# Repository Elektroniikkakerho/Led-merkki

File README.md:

# LED-MERKKI

## Mistä koostuu ja miten se toimii
Salaman mikrokontrolleri (mcu) ohjaa ledejä sytyttäen niitä yksi kerrallaan hyvin lyhyeksi aikaa.
Ledit ovat multiplexattu (4x8 LED), ja kytketty yhdellä vastuksella per rivi.

Levyyn on myös suunniteltu kytkin, jolla voisi vaikka sammuttaa laitteen tai toimittaa muuta toiminnallisuutta, mutta näitä ei ole koodissa toteutettu vieläkään.

Kuusipinninen liitin on ohjelmointia varten ja sitä kautta ohjelma siirretääm mikrokontrollerille.
Ohjelmointi hoituu Arduinon ISP:n kautta.

## Skeema

## Osaluettelo
<!--
  * 1 kpl  ATtiny861a SOIC
  * 32 kpl 3 mm diffusoitu LED
  * 1 kpl  10 µF SMD tantaalikondensaattori
  * Kuusi pinnisen piikkiriman ohjelmointia varten.

  **Riippuen LEDien väristä:**
  * Siniset/valkoiset/vihreät:   4 kpl 110 Ohm 1206/1210 SMD-vastus
  * Punaiset/keltaiset:          4 kpl 150 Ohm...
  
  **lisäksi tarvitset:**
  * kuumaliimaa
  * USB kaapelin
  * Extra vastuksen? Selivä myöhemmin...
  * haalarimerkin :-)
-->

| **Komponetti** | **KPL** | **Huomautukset** |
| :--- | :--- | :--- |
| ATtiny861a SOIC | 1 |  |
| 3 mm diffusoitu LED | 32 | |
| 110 Ohm 1206/1210 SMD vastus | 4 | Sinisille, valkoisille, vihreille ledeille |
| 169 Ohm 1206/1210 SMD vastus | 4 | Keltaisille, punaisille ledeille |
| 10 µF SMD tantaalikondensaattori | 1 | |
| 6 pinnisen piikkirima | - | Ohjelmointia varten |
| Kuumaliimaa | - | Ledien suojaamiseen |
| USB kaapeli | - | Sopivan pituinen, vaikka 1 m |
| Haalarimerkki | 1 | :-) |

<!---
| **Komponetti** | **KPL** | **Huomautukset** |
| :--- | :--- | :--- |
| ATtiny861a SOIC | 1 | S/SU |
| 3 mm diffusoitu LED | 32 | |
| 10 µF SMD tantaalikondensaattori | 1 | |

| **Vastuksets** | **KPL** | **Huomautukset** |
 :--- | :--- | :--- |
| 110 Ohm 1206/1210 SMD vastus | 4 | Sinisille, valkoisille, vihreille ledeille |
| 150 Ohm 1206/1210 SMD vastus | 4 | Keltaisille, punaisille ledeille |
| | | | 

| **Lisäksi tarvitset** | |
 :--- | :--- |
| 6 pinnisen piikkirima | ohjelmointia varten |
| Kuumaliimaa | Ledien suojaamiseen |
| USB kaapelin | Sopivan pituinen |
| Haalarimerkin  | :-) |
--->
  
## Pirilevyt 
| [SIK](kicad/possu) | OTiT | [YRK](kicad/ymp) | [PROSE](kicad/prose) | [KONE](kicad/kone) | [ARK](kicad/ark) | [OPTIEM](kicad/optiem) |
| :---: | :---: | :---: | :---: |  :---: |  :---: |  :---: |
|   |   |   |  |  |  |  <tr></tr>
|  |  |  |  |  |   | 
<!---|   |   |   |   | | | <tr></tr> --->

<!-- ## Ohjeet piirilevyn tekoon -->
<!-- <details> -->
<!-- <summary><b>Näytä </b></summary> -->
<!-- Tee vaikka syövyttämällä tai jyrsimällä :D -->
<!-- </details> -->

# Ohjeet kokoonpanoon

Nyt kun sinulla on piirilevy, laitetaampa siihen komponentit kiinni.

## 1. Pintaliitos komponentit

Piirilevyyn juotetaan 4 SMD vastusta, 1 SMD kondensaattori ja 6-pinninen piikkirimai.  
Helpointen ja nätein tapa juottaa ne on laittamalla yhteen pädiin vähän tinaa ja sitten     varovasti työntää komponetti sulaneseen tinaan, niin ettei se jää "ilmaan".  
Toinen puoli on helpompi juottaa kun se nyt pysyy siinä paikallaan.

Vastuksilla ei ole väliä kummin päin ne on laitettu, kuhan numero puoli on ylöspäin ja suhteellisen suoraan laitettu, se on hyvä.
Kondensaattorin suunta pitää kattoa leiskasta.

Piikkiriman juottaminen onnistuu samalla tavalla, paitsi nyt joudut pitämään sitä vähän ilmassa,  
jotta saat sen kunnolla juotettua kiinni.

## 2. Piiri 
Piirin juottaminen onnistuu helpointen siten, että juotat ensin yhden kulmajalan kiinni.  
Sulata juotos, jos piiri on vinossa.
Tarkista, että piirin kaikki jalat ovat pädien päällä. Ei ilmassa.  
Juota sitten toinen vastakkainen kulmajalma.

Loput jalat voi juottaa yksi kerrallaan.  
Tai jos haluaa kokeilla nopeammalla tavalla niin veto juottamalla saa yhden puolen yhdellä vedolla*. 
[Esimerkki video...](https://www.youtube.com/results?search_query=drag+soldering)

## 3. Virtajohto
USB kaapelista pitää leikata toinen pää pois.  
Kuori 5v and GND johdot joko saksilla tai kuorimilla.  
Juota sitten 5V ja GND piirilevyyn.

Tähän kannattaa käyttää USB-kaapelia, jossa on vain 5V ja GND.   
Tai sellaista kaapelia jossa on paksut sisäiset johtimet.

## 4. Ledit

Ledien juottaminen on suurin työmaa merkin valmistuksessa.  
Työtä aiheuttaa lähinnä ledin painaminen merkistä läpi. Ensin pitää huomioida polariteetti.  
Jos olet nähnyt paljon vaivaa että olet laittanut ledit miten sattuu niin voipi harmittaa..

**Pidä mielessä:**  
Pyöreä läpiveto ja pidempi jalka ledissä = POS  
Neliö läpiveto ja lyhyempi jalka ledissä = NEG

Ledien jalkojen päät kannattaa katkoa kulmassa, näin niistä tulee teräviä. Helpottaa ledien painamista merkistä läpi.
Toinen kikka on myös paksummalla neulalla tehä reikiä etukäteen.

Jos jostakin syystä, olet juottanut kaikki ledin väärin päin.  
Erinomaista, homma meni pieleen.  
Onneksi on olemassa toinen koodi tiedosto joka vaihtaa ledien logiikan.
   
## [5. Hyppää kohtaan "Ohjelmointi"](#ohjelmointi)
   
## 6. Piikkiriman poisto
Sitten kun ohjelmisto on flashatty ja tarkistettu, että kaikki ledit toimiii niinkuin pitäisi, piikkirima otetaan pois. Joko imusukkaa / tinapumppua käyttäen tai sitten lämmittämällä kaikki joloissa olevat tinat kolvilla, tekemällä vetoliikkeitä.
    
## 7. Kuormavastus 
Tässä kohtaan on hyvä kokeilla laittaa merkki powerbankkiin kiinni.

Jos merkki sammuu itsestään, se voi hyvinkin johtua siitä, että merkki on liian energiatehokas :D
Esim. SIK:in possu merkki syöpi n. 5-20 ma riippuen ledien tilasta.

Tämän ongelman saa korjattua juottamalla kuormavastuksen 5V ja GND väliin.  
Esim. Juottamalla 110 ohmin vastuksen, merkki syö ~60 ma.  
Tarvittava kuormavastus riippuu käyttämästäsi varavirtalähteestä.  
Niissä on vaihteleva minimivirranvaatimus, jonka alittaessa ne katkaisevat virransyötön.
    
## 8. Viimeistely
Lopuksi, laita kuumaliimaa ledien ympärille suojausta varten.  
Ei ole pakko jos et halua.

Mutta siinähän ois ***komia*** merkki valmiina.  
Ei muuta ku ompelemaan kiinni!!  
🥳 🧵 🪡

<!-- </details> -->

# Ohjelmointi

Tähän tarvitset Arduino nanon tai unon, jotta saat siirrettyä koodit levylle.

Koodin kääntämiseen tarvitset avr-gcc ja koodin siirtämiseen avrdude.  
Eli asenna omalle käyttöjärjestelmälle kyseiset työkalut, ennen seuraavia kohtia.

## 1. Ohjelmoinin setuppaus
Aletaanpa pukata sitä koodia, että merkkistä tulisi valoa.  
Mutta ensin pitää hyppyjohdoilla tehdä yhteys led-merkkiin.

Käytetään Arduino nanoa tässä esimerkissä:

| Merkin pinni | 1 | 2| 3 | 4 |5 |6 |
| :---: | :---: | :---: | :---: | :---: | :---: | :---: |
| *Selite* | *MOSI* | *MISO* | *SCK* | *VCC* | *GND* | *Reset* <tr></tr> |
| **Arduinon pinni** | **D11** | **D12**| **D13** | **VCC** | **GND** | **D10** | 

(Leiska kuvasta näkee liittimessä neliön --> 1. pinni)

Muista vetää arduinon Reset ylös. Ardu nollautuu kun sarjaliikenne alotetaan....

## 2. Ledien suunta logiikan flippaus
Mikäli olet juottanut ledit väärinpäin, eikä niiden irroittaminen ja uudelleen juottaminen huvita,  
voit muuttaa ledien ohjaavan logiikan ennen kääntämistä.
      
**Tiedosto: led-merkki/src/vilkutus.c**  
(rivit 6-7):

```c
#include "lediportit.h"             // Mikäli juotit ledit väärin päin,
// #include "lediportit_vaarin.h"   // Vaihda tästä otsikko tiedosto.
  ```
Ledit väärinpäin: 
```c
// #include "lediportit.h"             // Mikäli juotit ledit väärin päin,
#include "lediportit_vaarin.h"   // Vaihda tästä otsikko tiedosto.       
```

## 3. Koodin kääntäminen

```bash
# Kääntäminen käyttäen avr-gcc:tä
avr-gcc -mmcu=attiny861 salama.c -I./ -Os -DF_CPU=8000000UL
```

  Jos et saa koodeja käännettyä,  pre_compiled hakemistosta löytyy valmiiksi käännetyt koodit. 
    
## 4. Ohjelman siirto levylle 

#####  Unix-like

```bash
# Fläsäys käyttäen arduino-isp:tä
avrdude -c avrisp -p t861 -B3 -P /dev/ttyUSB0 -b 19200 -U flash:w:a.out

# Fuse asetukset käyttäen arduino-isp:tä
avrdude -c avrisp -p t861 -B3 -P /dev/ttyUSB0 -b 19200 -U lfuse:w:0xe2:m -U hfuse:w:0xdf:m
```
Jos valittaa oikeuksista, vedä sudo/doas tilassa.

Jos siirtämisen aikana tulee "programmer not responding",  
kokeile toista baudratea tai ottamalla "-B3" pois.

##### Windows

```bash
# Fläsäys käyttäen arduino-isp:tä
avrdude -c avrisp -p t861 -P COM3 -b 19200 -U flash:w:a.out

# Fuse asetukset käyttäen arduino-isp:tä
avrdude -c avrisp -p t861 -P COM3 -b 19200 -U lfuse:w:0xe2:m -U hfuse:w:0xdf:m

```
Windowsilla avrdude pitää olla ympäristömuuttujissa.  
Toinen vaihtoehto on ajaa komento "\Arduino\hardware\tools\avr\bin"-kansiossa.

Jos siirtämisen aikana tulee error,  
kokeile toista baudratea tai lisäämällä "-B3" kuten Unix-like komennoissa.

## [5. Hyppää kohtaan "Piikkiriman poisto"](#6-piikkiriman-poisto)

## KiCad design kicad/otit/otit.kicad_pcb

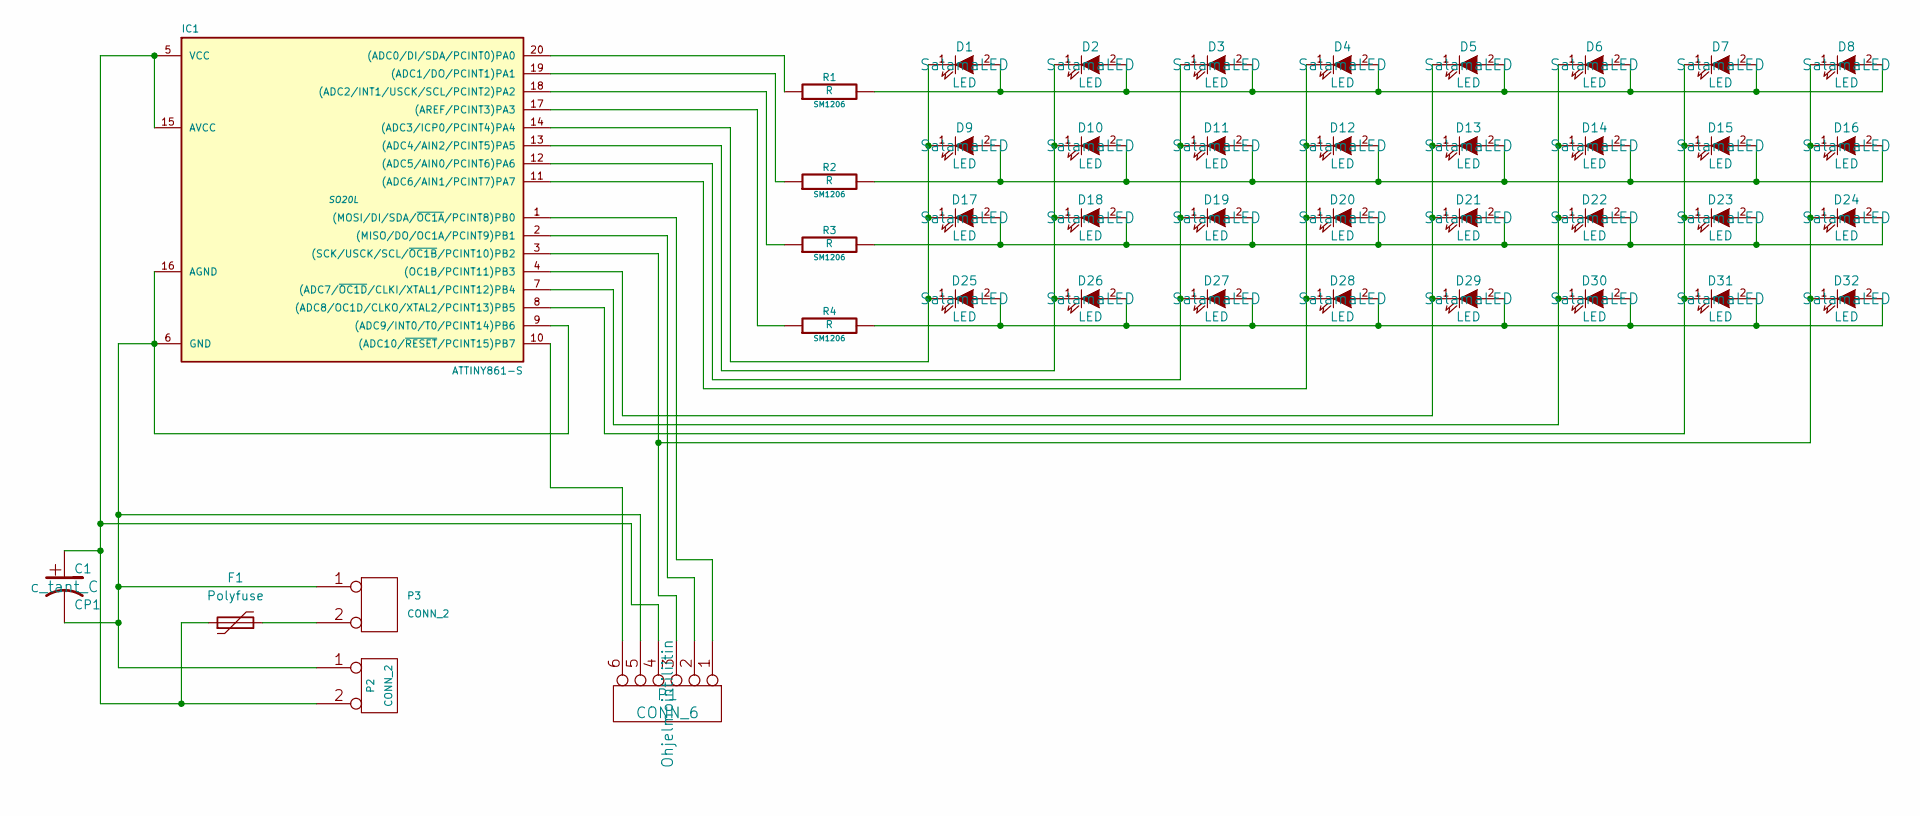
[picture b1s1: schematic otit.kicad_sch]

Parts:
C1: CP1; c_tant_C
D1, D2, D3, D4, D5, D6, D7, D8, D9, D10, D11, D12, D13, D14, D15, D16, D17, D18, D19, D20, D21, D22, D23, D24, D25, D26, D27, D28, D29, D30, D31, D32: LED; SalamaLED
F1: Polyfuse
IC1: ATTINY861-S; SO20L
P1: CONN_6; Ohjelmointiliitin
P2: CONN_2; Salama_virta
P3: CONN_2
R1, R2, R3, R4: R; SM1206

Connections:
unnamed: D1.2 (A), D2.2 (A), D3.2 (A), D4.2 (A), D5.2 (A), D6.2 (A), D7.2 (A), D8.2 (A), R1.2
unnamed: D1.1 (K), D9.1 (K), D17.1 (K), D25.1 (K), IC1.14 ((ADC3/ICP0/PCINT4)PA4)
unnamed: D9.2 (A), D10.2 (A), D11.2 (A), D12.2 (A), D13.2 (A), D14.2 (A), D15.2 (A), D16.2 (A), R2.2
unnamed: D2.1 (K), D10.1 (K), D18.1 (K), D26.1 (K), IC1.13 ((ADC4/AIN2/PCINT5)PA5)
unnamed: D3.1 (K), D11.1 (K), D19.1 (K), D27.1 (K), IC1.12 ((ADC5/AIN0/PCINT6)PA6)
unnamed: D4.1 (K), D12.1 (K), D20.1 (K), D28.1 (K), IC1.11 ((ADC6/AIN1/PCINT7)PA7)
unnamed: D5.1 (K), D13.1 (K), D21.1 (K), D29.1 (K), IC1.4 ((OC1B/PCINT11)PB3)
unnamed: D6.1 (K), D14.1 (K), D22.1 (K), D30.1 (K), IC1.7 ((ADC7/~OC1D/CLKI/XTAL1/PCINT12)PB4)
unnamed: D7.1 (K), D15.1 (K), D23.1 (K), D31.1 (K), IC1.8 ((ADC8/OC1D/CLKO/XTAL2/PCINT13)PB5)
unnamed: D8.1 (K), D16.1 (K), D24.1 (K), D32.1 (K), IC1.3 ((SCK/USCK/SCL/~OC1B/PCINT10)PB2), P1.3
unnamed: D17.2 (A), D18.2 (A), D19.2 (A), D20.2 (A), D21.2 (A), D22.2 (A), D23.2 (A), D24.2 (A), R3.2
unnamed: D25.2 (A), D26.2 (A), D27.2 (A), D28.2 (A), D29.2 (A), D30.2 (A), D31.2 (A), D32.2 (A), R4.2
unnamed: F1.2, P3.2 (PM)
unnamed: IC1.20 ((ADC0/DI/SDA/PCINT0)PA0), R1.1
unnamed: IC1.19 ((ADC1/DO/PCINT1)PA1), R2.1
unnamed: IC1.18 ((ADC2/INT1/USCK/SCL/PCINT2)PA2), R3.1
unnamed: C1.2, IC1.6 (GND), IC1.9 ((ADC9/INT0/T0/PCINT14)PB6), IC1.16 (AGND), P1.5, P2.1, P3.1
unnamed: IC1.10 ((ADC10/~RESET/PCINT15)PB7), P1.6
unnamed: IC1.17 ((AREF/PCINT3)PA3), R4.1
unnamed: IC1.2 ((MISO/DO/OC1A/PCINT9)PB1), P1.2
unnamed: IC1.1 ((MOSI/DI/SDA/~OC1A/PCINT8)PB0), P1.1
unnamed: C1.1, F1.1, IC1.5 (VCC), IC1.15 (AVCC), P1.4, P2.2 (PM)

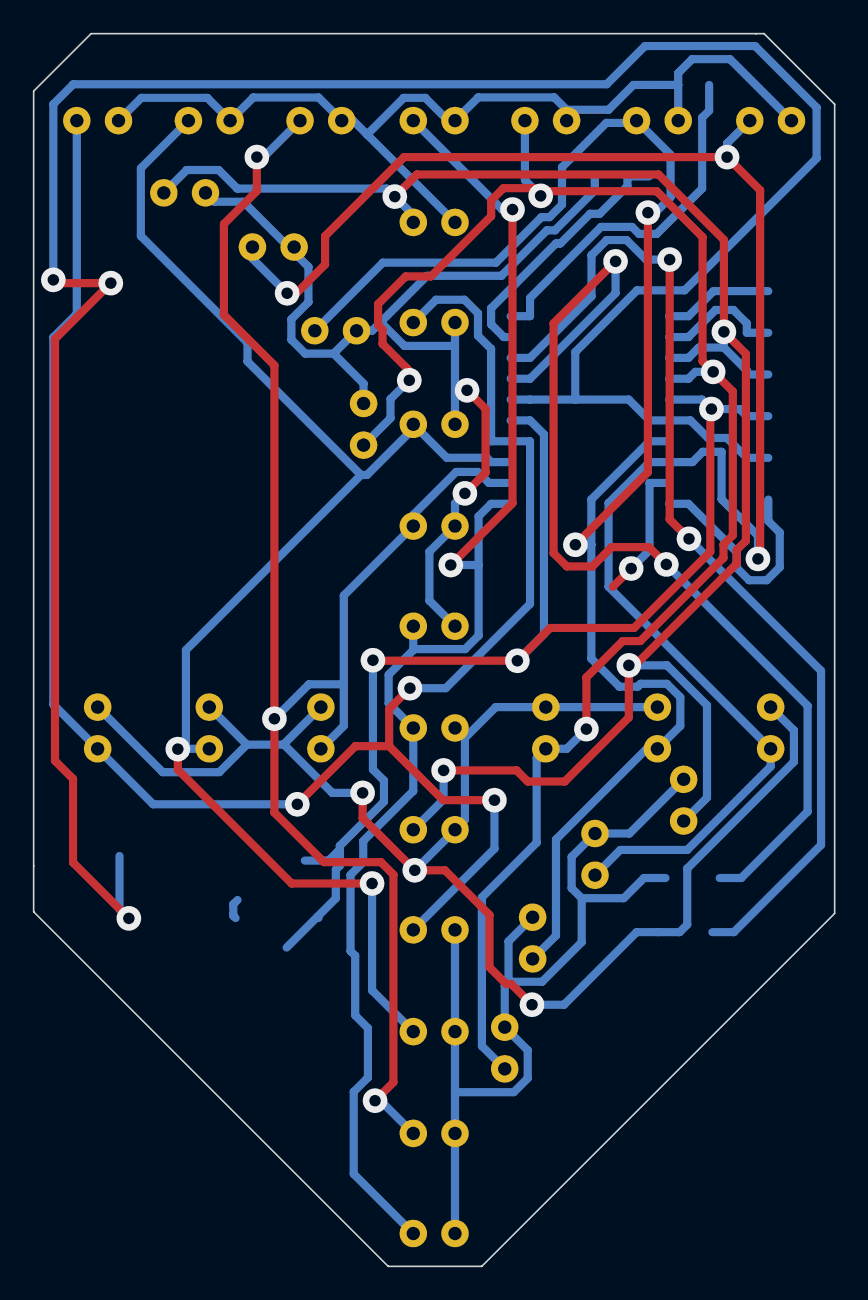
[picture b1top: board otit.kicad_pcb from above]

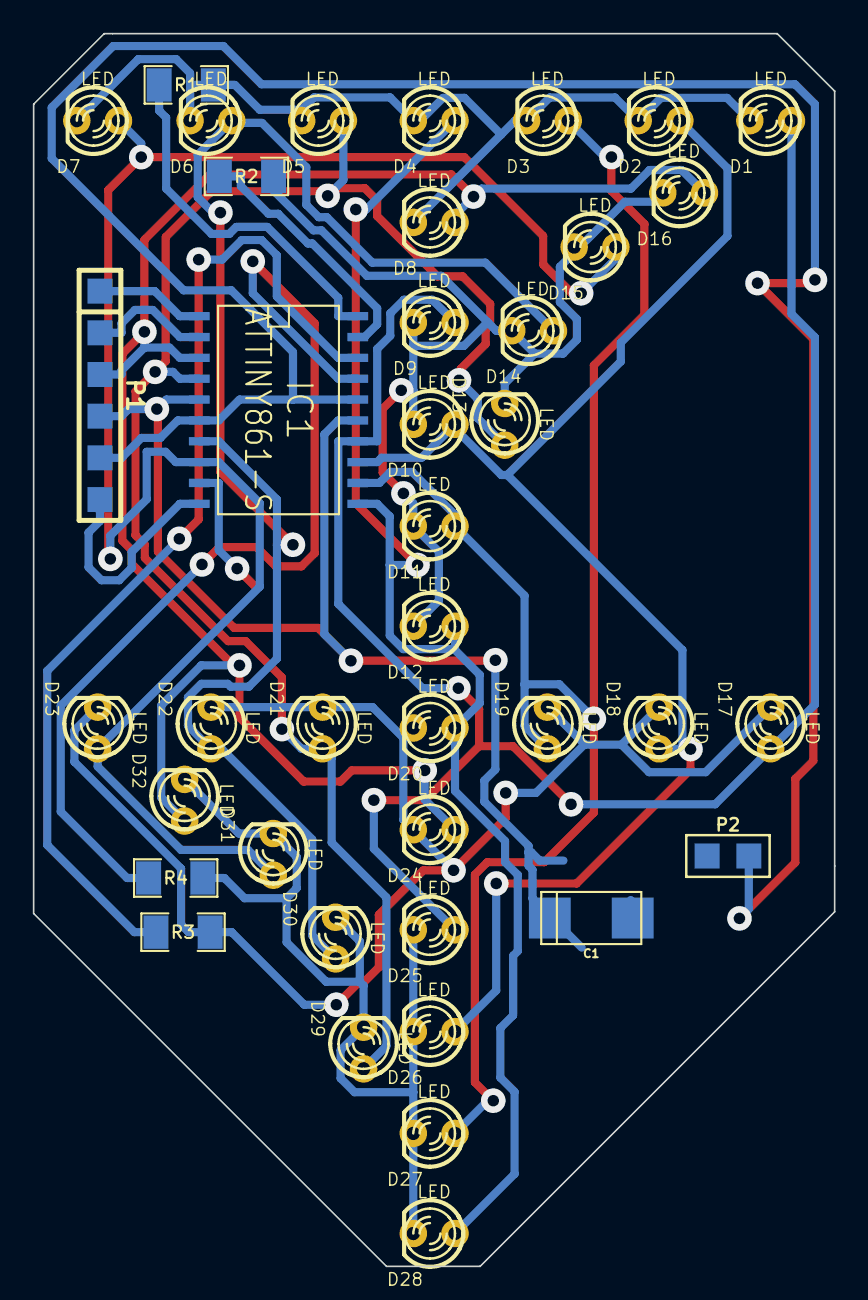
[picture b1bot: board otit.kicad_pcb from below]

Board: 2 copper layers, 48.8 x 75.1 mm, 40 parts (40 on the bottom side), 21 nets.

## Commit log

2025-09-02 Lisätty muitten kiltojen gerbereita
2025-09-02 rename dirs
2025-09-11 Rename salama.jpg to kuvia/salama.jpg
2025-09-14 Lisätty tekstiä readmen alkuun
2025-09-14 Rename kuvia/skeema.svg to kicad/kuvat/skeema.svg
2025-09-19 README.md Päivitys
    Update README.md
    Update README.md
    Update README.md
    Lisätty muitten kiltojen gerbereita
    rename dirs
    Update README.md
2025-12-03 Kicadi projekti tiedostoja siirretty omiin kansioihin
2025-12-14 Nyt src koodit kääntyy
    Vedin "diff src/ src_windows/" ja huomasin, että ne ovat käytännössä
    samoja. Poistin src_windows.
    Korjasin src koodit kääntyviksi.
    Lisäsin otsikkotiedoston "vilkutus.c" kuviot.c:hen.
    Kääntäminen onnistuu samalla avr-gcc komennolla mitä aikasemmin, paitsi vilkutus.c jää
    pois.
2026-03-23 Update README.md
    päivitetty koodi Windowsille
